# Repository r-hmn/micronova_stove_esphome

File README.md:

# micronova_stove_esphome
Three sub-projects for connecting a home automation system to ARTEL IDRO15 PelletStove.
1. Kicad PCB for 'ESP32 mini D1'.
2. Arduino-code for reading all RAM- and EEPROM-registers easily.
3. ESPHOME-yaml for connecting the PelletStove to e.g. Home Assistent or OpenHAB.

## Contained projects:

### 1) Kicad `stove-reader-pcb`
A Kicad project for PCB to fit an 'ESP32 mini D1' to communicate with a PelletStove having a MicroNova compatible serial interface.

The PCB has JST-XH2.54 connectors for
- 2x I2C devices
- 2x external DSB18B20 temperature sensors
- 1x for power conversion
- 1x pelletstove serial

### 2) Arduino `stove-ram-reader`
I created it to find the correct address of the Fume-Temperature address for my stove type.

Works in combination with the PCB.
Code is for ArduinoIDE 2.x to program an 'ESP32 mini D1'.
Program to interrogate the RAM and EEPROM registers and publishes it via its webserver.
Its address is published via mDNS as `esp32.local`
Webserver can be accessed at http://esp32.local/

Uses a version of:
- `micronova_stove.h` code from https://github.com/eni23/micronova-controller
- `micronova_stove.cpp` code from https://github.com/eni23/micronova-controller

### 3) ESPHOME yaml
Works in combination with the PCB.

YAML which interfaces with 
- OLED screen for local readout (i2c OLED 128x32).
- Pellet level sensor (i2c VL53L0X time-of-flight infrared distance sensor).
- External temperature sensors (In below image the DSB18B20's are not connected).

## Related info:
- https://github.com/eni23/micronova-controller
- https://esphome.io/components/micronova/

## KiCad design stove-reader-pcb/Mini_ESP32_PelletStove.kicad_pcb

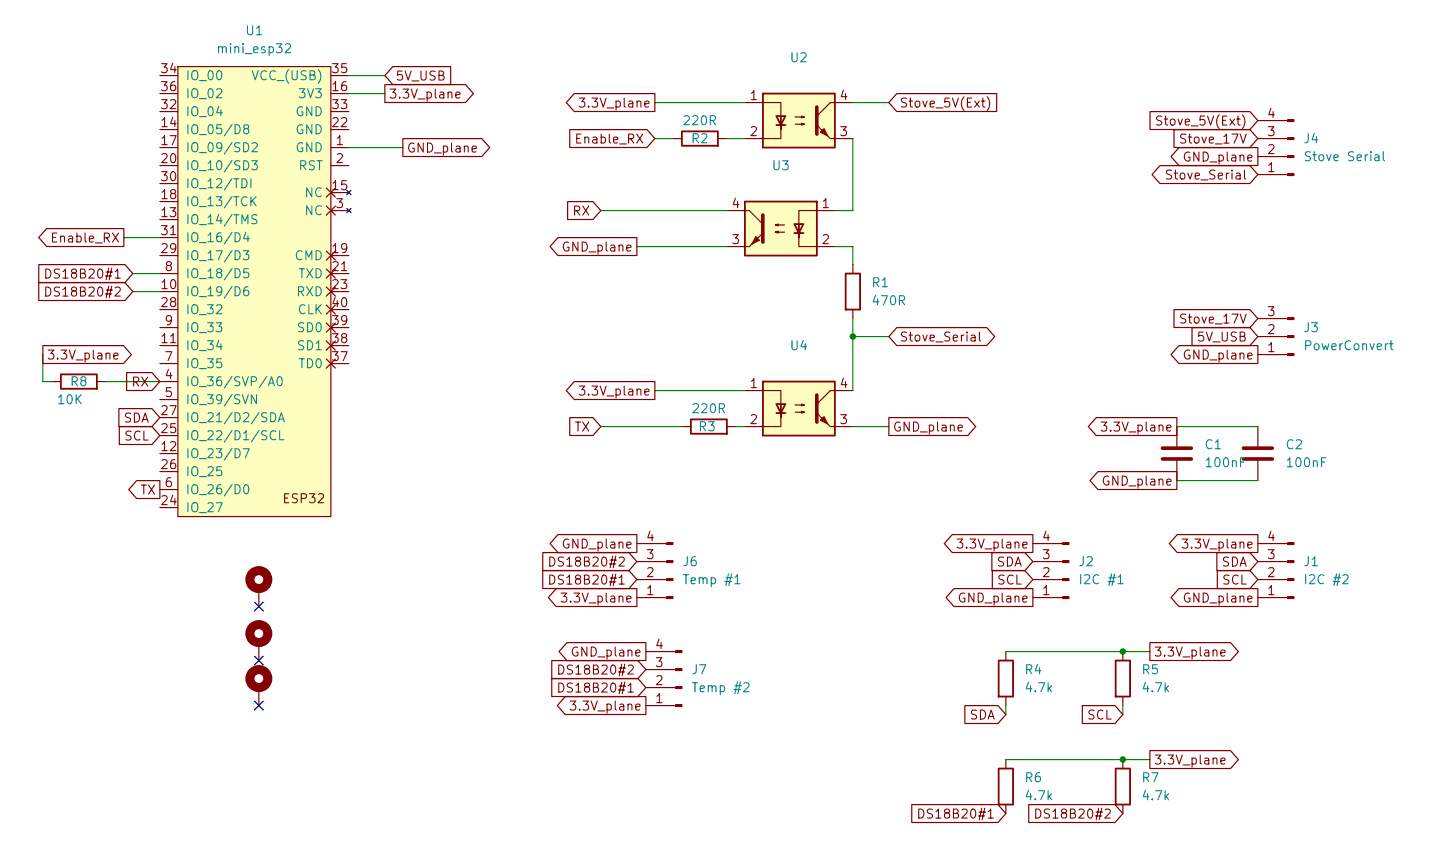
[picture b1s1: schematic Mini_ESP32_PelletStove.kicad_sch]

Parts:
C1, C2: 100nF; C_Rect_L7.0mm_W2.5mm_P5.00mm
H1, H2, H3: MountingHole_Pad; MountingHole_3.2mm_M3_DIN965_Pad
J1: I2C #2; JST_XH_B4B-XH-A_1x04_P2.50mm_Vertical
J2: I2C #1; JST_XH_B4B-XH-A_1x04_P2.50mm_Vertical
J3: PowerConvert; JST_XH_B3B-XH-A_1x03_P2.50mm_Vertical
J4: Stove Serial; JST_XH_B4B-XH-A_1x04_P2.50mm_Vertical
J6: Temp #1; JST_XH_B4B-XH-A_1x04_P2.50mm_Vertical
J7: Temp #2; JST_XH_B4B-XH-A_1x04_P2.50mm_Vertical
R1: 470R; R_Axial_DIN0207_L6.3mm_D2.5mm_P7.62mm_Horizontal
R2, R3: 220R; R_Axial_DIN0207_L6.3mm_D2.5mm_P7.62mm_Horizontal
R4, R5, R6, R7: 4.7k; R_Axial_DIN0207_L6.3mm_D2.5mm_P7.62mm_Horizontal
R8: 10K; R_Axial_DIN0207_L6.3mm_D2.5mm_P7.62mm_Horizontal
U1: mini_esp32; ESP32_mini-HAT
U2, U3, U4: SFH617A-4X006; DIP-4_W7.62mm

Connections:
3.3V_plane: C1.1, C2.1, J1.4, J2.4, J6.1, J7.1, R4.1, R5.1, R6.1, R7.1, R8.1, U1.16 (3V3), U2.1, U4.1
5V_USB: J3.2, U1.35 (VCC_(USB))
DS18B20#1: J6.2, J7.2, R6.2, U1.8 (IO_18/D5)
DS18B20#2: J6.3, J7.3, R7.2, U1.10 (IO_19/D6)
Enable_RX: R2.1, U1.31 (IO_16/D4)
GND_plane: C1.2, C2.2, J1.1, J2.1, J3.1, J4.2, J6.4, J7.4, U1.1 (GND), U3.3, U4.3
unnamed: R1.1, U3.2
unnamed: R2.2, U2.2
unnamed: R3.2, U4.2
unnamed: U2.3, U3.1
RX: R8.2, U1.4 (IO_36/SVP/A0), U3.4
SCL: J1.2, J2.2, R5.2, U1.25 (IO_22/D1/SCL)
SDA: J1.3, J2.3, R4.2, U1.27 (IO_21/D2/SDA)
Stove_5V(Ext): J4.4, U2.4
Stove_17V: J3.3, J4.3
Stove_Serial: J4.1, R1.2, U4.4
TX: R3.1, U1.6 (IO_26/D0)

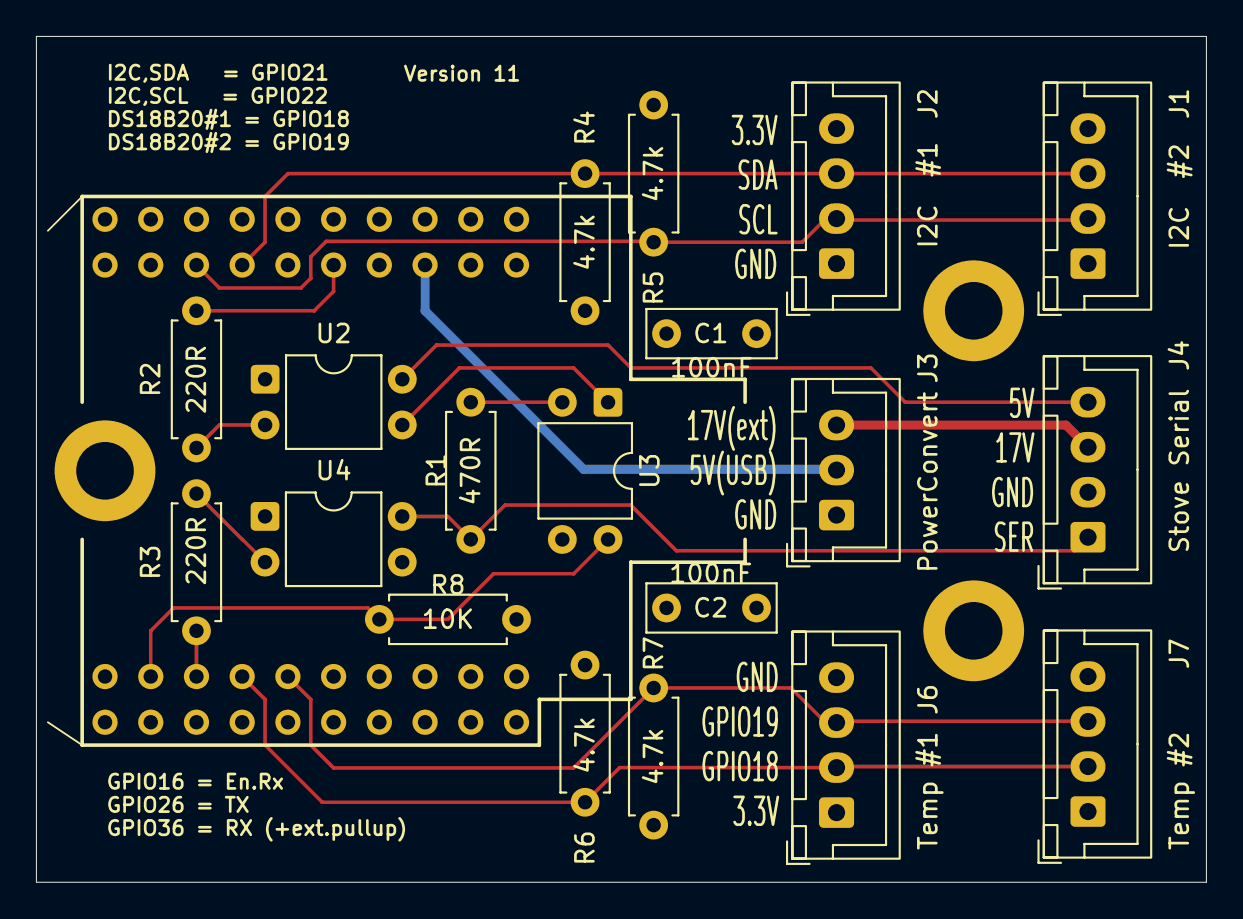
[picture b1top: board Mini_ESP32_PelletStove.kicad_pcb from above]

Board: 4 copper layers, 65.0 x 47.0 mm, 23 parts (0 on the bottom side), 17 nets.

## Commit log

2026-05-03 First content
2026-05-09 Update micronova-pelletstove.yaml
    Set VLM timout to 100ms
